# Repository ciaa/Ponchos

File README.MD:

#Poncho IOT (Internet Of Things) para EDU-CIAA-NXP 

##Características Poncho

  - Módulo Wifi RN1810. Se utiliza mediante comandos por el puerto serial.
  - Dos salidas a Rele 220V-10A
  - Dos entradas optoacopladas
  - Sensor de temperatura analógico LM35
  
##Características PCB

El PCB fue pensado para ser construido manualmente, por lo que solo posee una capa (BOTTOM). La capa TOP solo indica jumpers que deben soldarse. Tambien es posible fabricarla en dos capas.
  
##Modelo 3D

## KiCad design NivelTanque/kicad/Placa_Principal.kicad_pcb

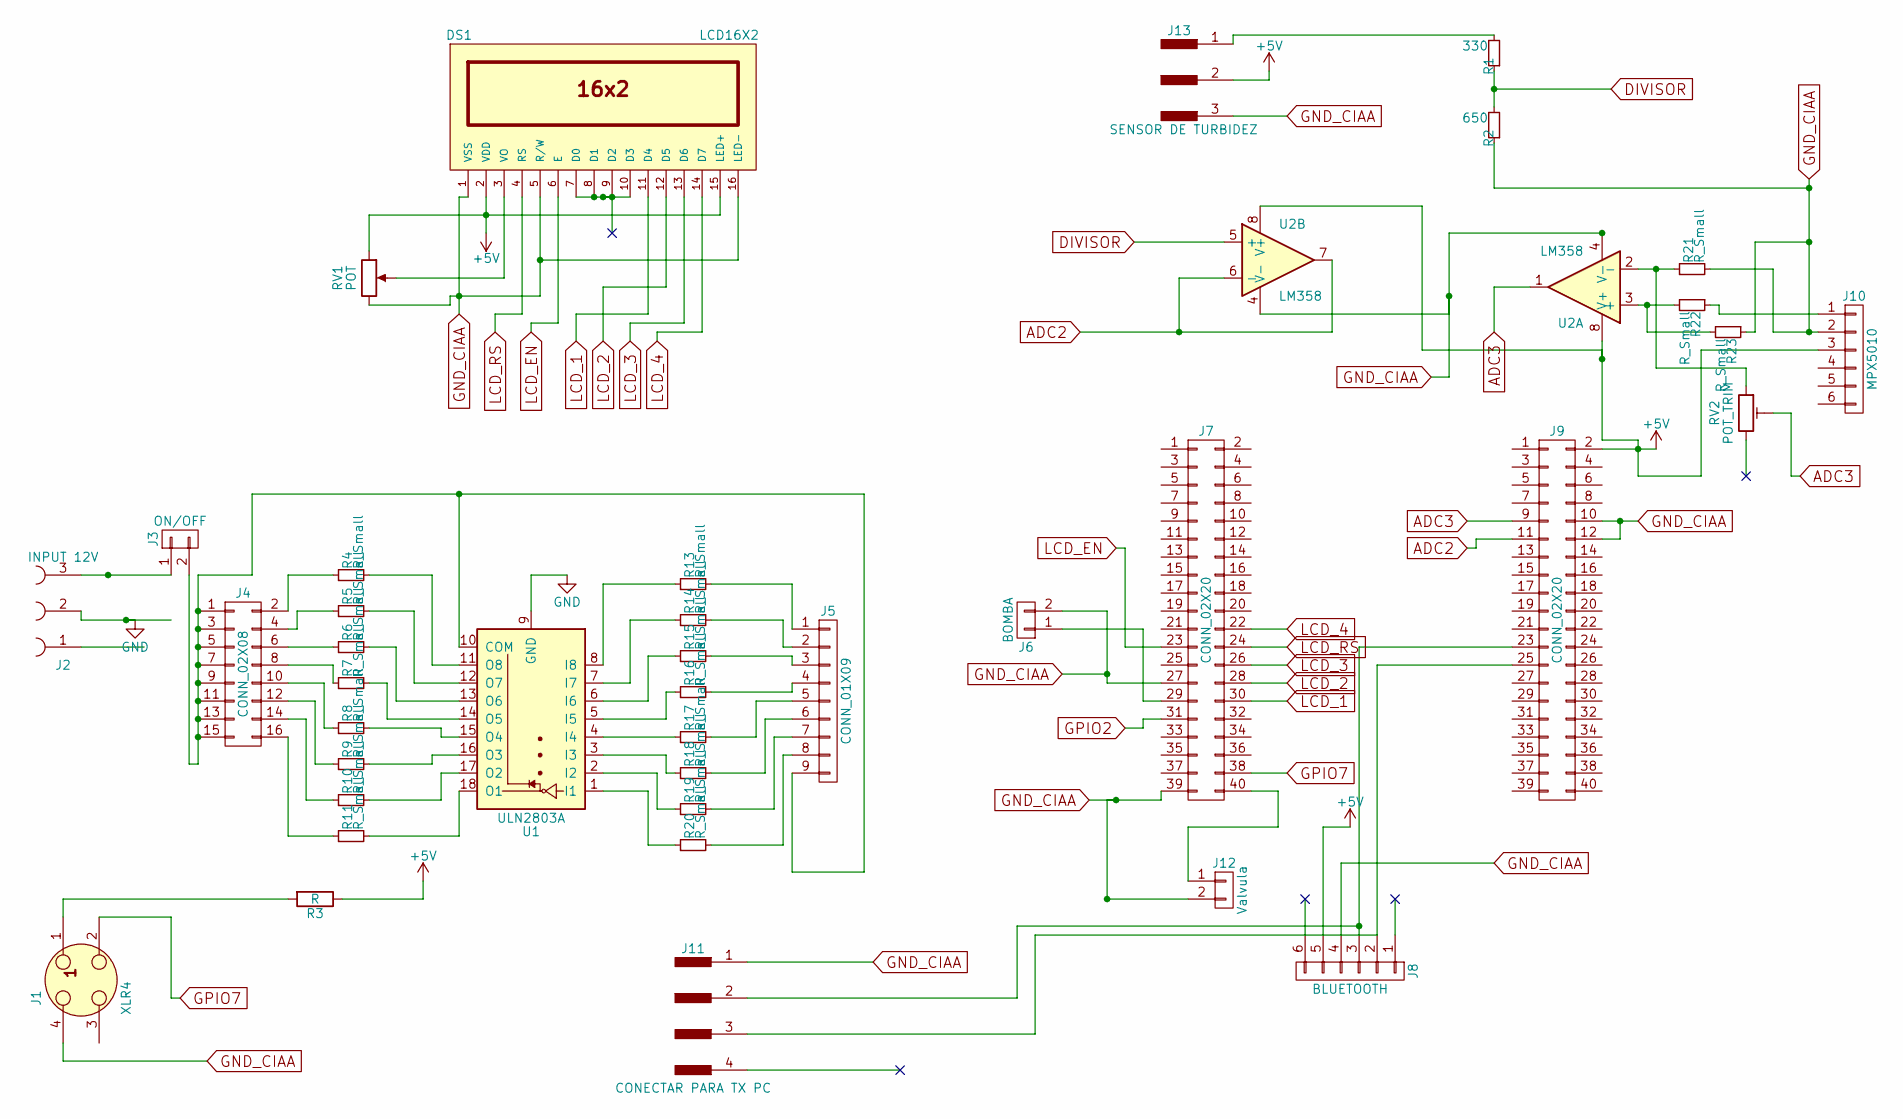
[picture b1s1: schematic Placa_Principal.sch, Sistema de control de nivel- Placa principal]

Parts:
DS1: LCD16X2; JST_XH_B16B-XH-A_16x2.50mm_Straight
J1: XLR4; Diode_Bridge_DIP-4_W7.62mm_P5.08mm
J2: INPUT 12V; TerminalBlock_bornier-3_P5.08mm
J3: ON/OFF; TerminalBlock_bornier-2_P5.08mm
J4: CONN_02X08; Pin_Header_Straight_2x08_Pitch2.54mm
J5: CONN_01X09; Pin_Header_Straight_1x09_Pitch2.54mm
J6: BOMBA; TerminalBlock_bornier-2_P5.08mm
J7, J9: CONN_02X20; Pin_Header_Straight_2x20_Pitch2.54mm
J8: BLUETOOTH; Pin_Header_Straight_1x06_Pitch2.54mm
J10: MPX5010; Pin_Header_Straight_1x06_Pitch2.54mm
J11: CONECTAR PARA TX PC; Pin_Header_Straight_1x04_Pitch2.54mm
J12: Valvula; TerminalBlock_bornier-2_P5.08mm
J13: SENSOR DE TURBIDEZ; Pin_Header_Straight_1x03_Pitch2.54mm
R1: 330; R_Axial_DIN0207_L6.3mm_D2.5mm_P15.24mm_Horizontal
R2: 650; R_Axial_DIN0207_L6.3mm_D2.5mm_P15.24mm_Horizontal
R3: R; R_Axial_DIN0207_L6.3mm_D2.5mm_P15.24mm_Horizontal
R4, R5, R6, R7, R8, R9, R10, R11, R13, R14, R15, R16, R17, R18, R19, R20, R21, R22, R23: R_Small; R_Axial_DIN0207_L6.3mm_D2.5mm_P15.24mm_Horizontal
RV1: POT; TerminalBlock_bornier-3_P5.08mm
RV2: POT_TRIM; Potentiometer_Trimmer_Bourns_3296W
U1: ULN2803A; DIP-18_W7.62mm_LongPads
U2: LM358; DIP-8_W7.62mm_LongPads

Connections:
+5V: DS1.2 (VDD), DS1.15 (LED+), J8.5, J9.2, J10.3, J13.2, R3.1, RV1.1, U2.8 (V+)
ADC2: J9.11, U2.6 (-), U2.7
ADC3: J9.9, RV2.2, U2.1
DIVISOR: R1.1, R2.2, U2.5 (+)
GND: J2.2, U1.9 (GND)
GND_CIAA: DS1.1 (VSS), DS1.5 (R/W), DS1.16 (LED-), J1.4, J6.2, J7.27, J7.39, J8.4, J9.10, J9.12, J10.2, J11.1, J12.2, J13.3, R2.1, R21.2, R23.1, RV1.3, U2.4 (V-)
GPIO2: J7.31
GPIO7: J1.2, J7.38
LCD_1: DS1.11 (D4), J7.30
LCD_2: DS1.12 (D5), J7.28
LCD_3: DS1.13 (D6), J7.26
LCD_4: DS1.14 (D7), J7.22
LCD_EN: DS1.6 (E), J7.23
LCD_RS: DS1.4 (RS), J7.24
unnamed: DS1.3 (VO), RV1.2
unnamed: DS1.7 (D0), DS1.8 (D1), DS1.9 (D2), DS1.10 (D3)
unnamed: J1.1, R3.2
unnamed: J2.3, J3.1
unnamed: J3.2, J4.1, J4.3, J4.5, J4.7, J4.9, J4.11, J4.13, J4.15, J5.9, U1.10 (COM)
unnamed: J4.2, R4.1
unnamed: J4.4, R5.1
unnamed: J4.6, R6.1
unnamed: J4.8, R7.1
unnamed: J4.10, R8.1
unnamed: J4.12, R9.1
unnamed: J4.14, R10.1
unnamed: J4.16, R11.1
unnamed: J5.1, R13.2
unnamed: J5.2, R14.2
unnamed: J5.3, R15.2
unnamed: J5.4, R16.2
unnamed: J5.5, R17.2
unnamed: J5.6, R18.2
unnamed: J5.7, R19.2
unnamed: J5.8, R20.2
unnamed: J6.1, J7.29
unnamed: J10.1, R22.1
unnamed: J8.3, J9.23, J11.2
unnamed: J8.2, J9.25, J11.3
unnamed: J7.40, J12.1
unnamed: J13.1, R1.2
unnamed: R4.2, U1.11 (O8)
unnamed: R5.2, U1.12 (O7)
unnamed: R6.2, U1.13 (O6)
unnamed: R7.2, U1.14 (O5)
unnamed: R8.2, U1.15 (O4)
unnamed: R9.2, U1.16 (O3)
unnamed: R10.2, U1.17 (O2)
unnamed: R11.2, U1.18 (O1)
unnamed: R13.1, U1.8 (I8)
unnamed: R14.1, U1.7 (I7)
unnamed: R15.1, U1.6 (I6)
unnamed: R16.1, U1.5 (I5)
unnamed: R17.1, U1.4 (I4)
unnamed: R18.1, U1.3 (I3)
unnamed: R19.1, U1.2 (I2)
unnamed: R20.1, U1.1 (I1)
unnamed: R21.1, RV2.1, U2.2 (-)
unnamed: R22.2, R23.2, U2.3 (+)

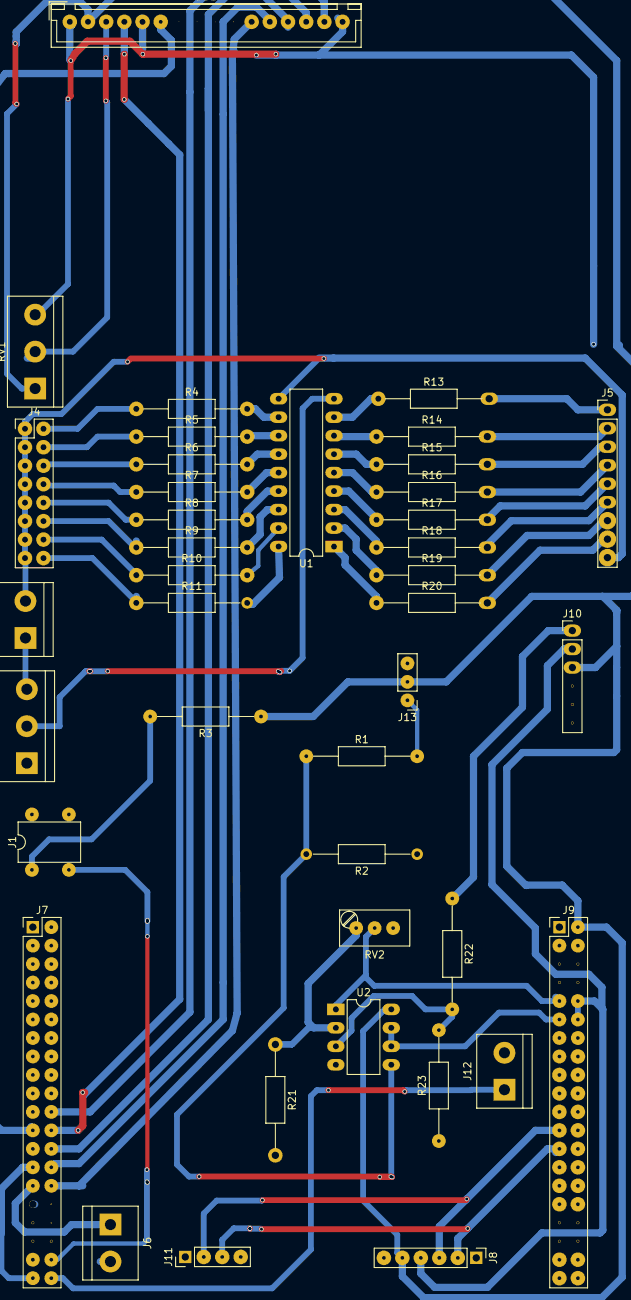
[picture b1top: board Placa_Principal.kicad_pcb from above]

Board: 2 copper layers, 40 parts (0 on the bottom side), 58 nets.

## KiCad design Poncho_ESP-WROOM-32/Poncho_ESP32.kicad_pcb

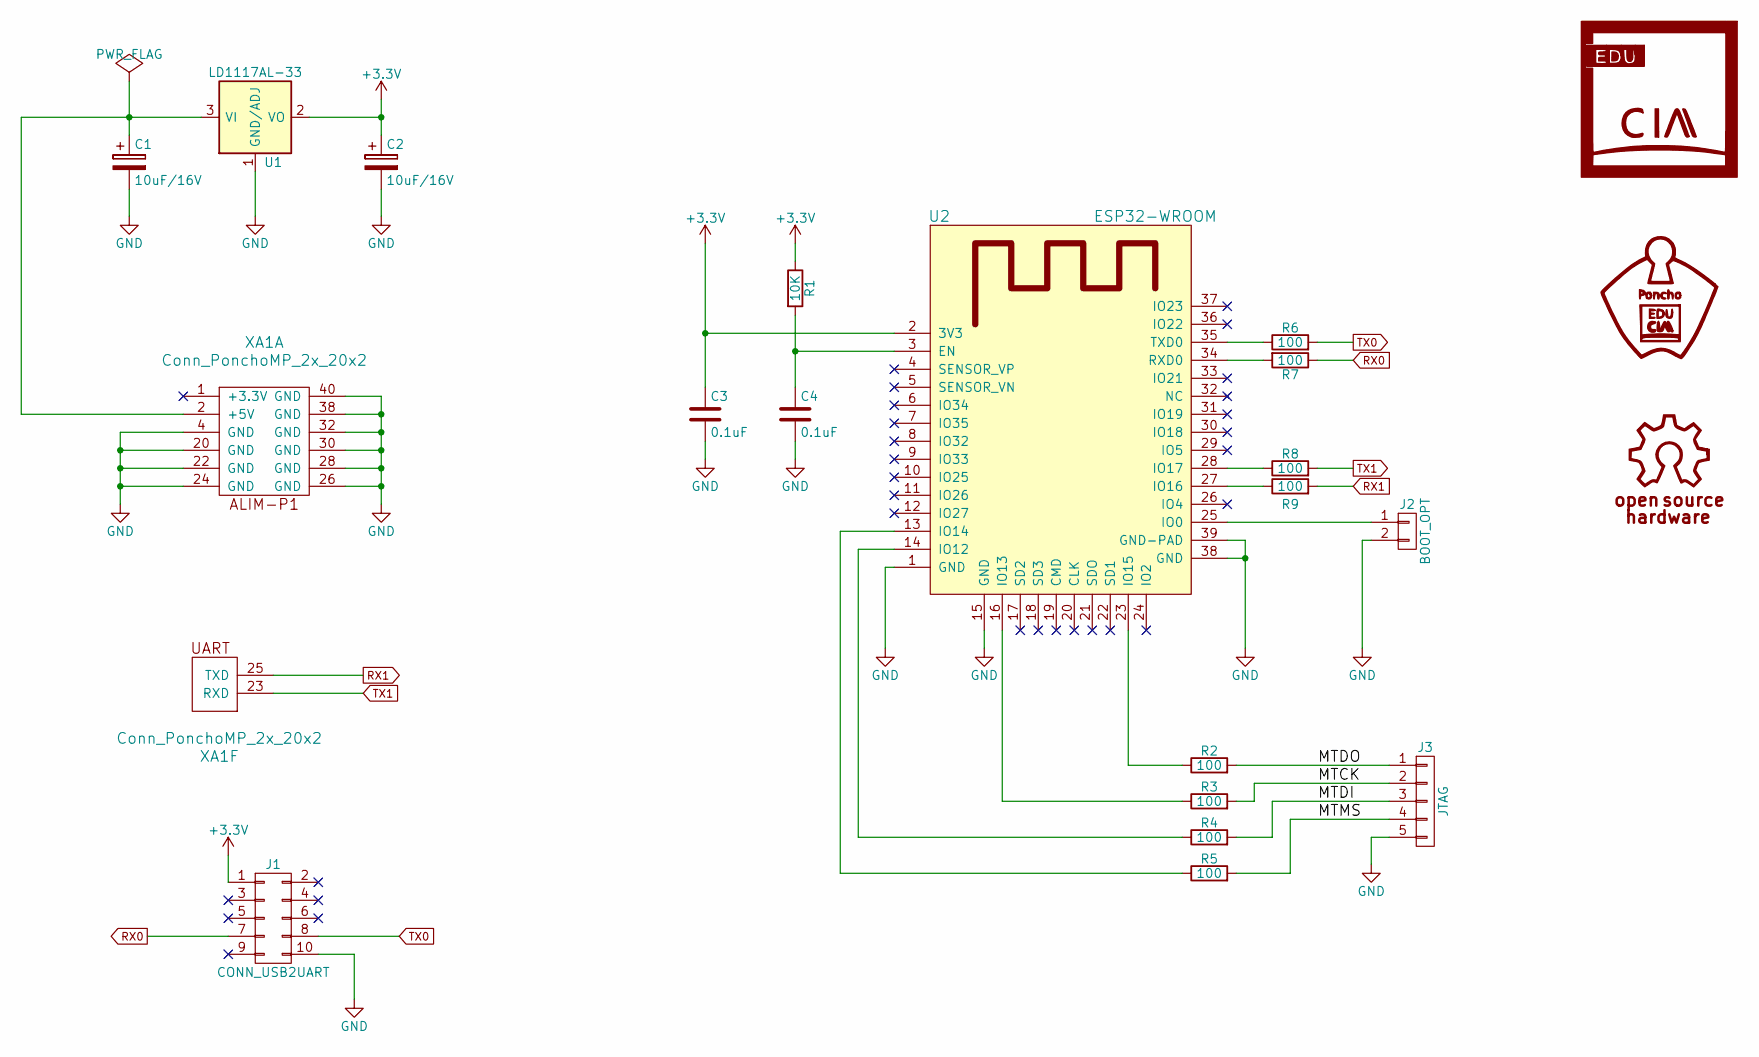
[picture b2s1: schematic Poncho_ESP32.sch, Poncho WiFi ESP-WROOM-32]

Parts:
C1, C2: 10uF/16V; CP_Elec_4x5.3
C3, C4: 0.1uF; C_0805_HandSoldering
J1: CONN_USB2UART; Socket_Strip_Angled_2x05_Pitch2.54mm
J2: BOOT_OPT; Pin_Header_Straight_1x02_Pitch2.54mm
J3: JTAG; Pin_Header_Straight_1x05_Pitch2.54mm
R1: 10K; R_0805_HandSoldering
R2, R3, R4, R5, R6, R7, R8, R9: 100; R_0805_HandSoldering
U1: LD1117AL-33; SOT-223
U2: ESP32-WROOM
XA1: Conn_PonchoMP_2x_20x2; Conn_Poncho_Derecha_Sin_Pin_Desc

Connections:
+3V3: C2.1, C3.1, J1.1, R1.1, U1.2 (VO), U1.4 (VO), U2.2 (3V3)
/MTCK: J3.2, R3.2
/MTDI: J3.3, R4.2
/MTDO: J3.1, R2.2
/MTMS: J3.4, R5.2
GND: C1.2, C2.2, C3.2, C4.2, J1.10, J2.2, J3.5, U1.1 (GND/ADJ), U2.1 (GND), U2.15 (GND), U2.38 (GND), U2.39 (GND-PAD), XA1.4 (GND), XA1.20 (GND), XA1.22 (GND), XA1.24 (GND), XA1.26 (GND), XA1.28 (GND), XA1.30 (GND), XA1.32 (GND), XA1.38 (GND), XA1.40 (GND)
unnamed: C1.1, U1.3 (VI), XA1.2 (+5V)
unnamed: C4.1, R1.2, U2.3 (EN)
unnamed: J2.1, U2.25 (IO0)
unnamed: R2.1, U2.23 (IO15)
unnamed: R3.1, U2.16 (IO13)
unnamed: R4.1, U2.14 (IO12)
unnamed: R5.1, U2.13 (IO14)
unnamed: R6.1, U2.35 (TXD0)
unnamed: R7.2, U2.34 (RXD0)
unnamed: R8.1, U2.28 (IO17)
unnamed: R9.1, U2.27 (IO16)
RX0: J1.7, R7.1
RX1: R9.2, XA1.25 (TXD)
TX0: J1.8, R6.2
TX1: R8.2, XA1.23 (RXD)

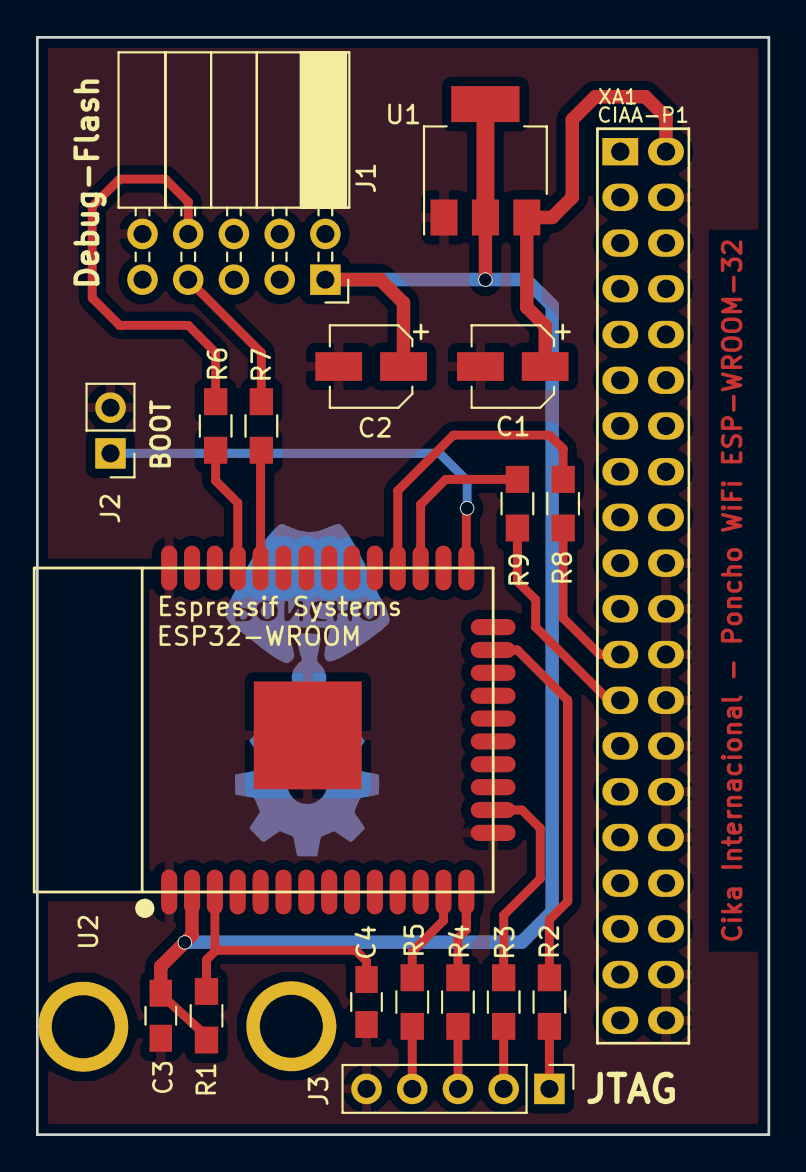
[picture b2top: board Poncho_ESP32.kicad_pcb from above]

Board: 2 copper layers, 40.6 x 61.0 mm, 21 parts (0 on the bottom side), 21 nets.

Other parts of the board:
H2, H2#2: PCB_HOLE; Led_Hole

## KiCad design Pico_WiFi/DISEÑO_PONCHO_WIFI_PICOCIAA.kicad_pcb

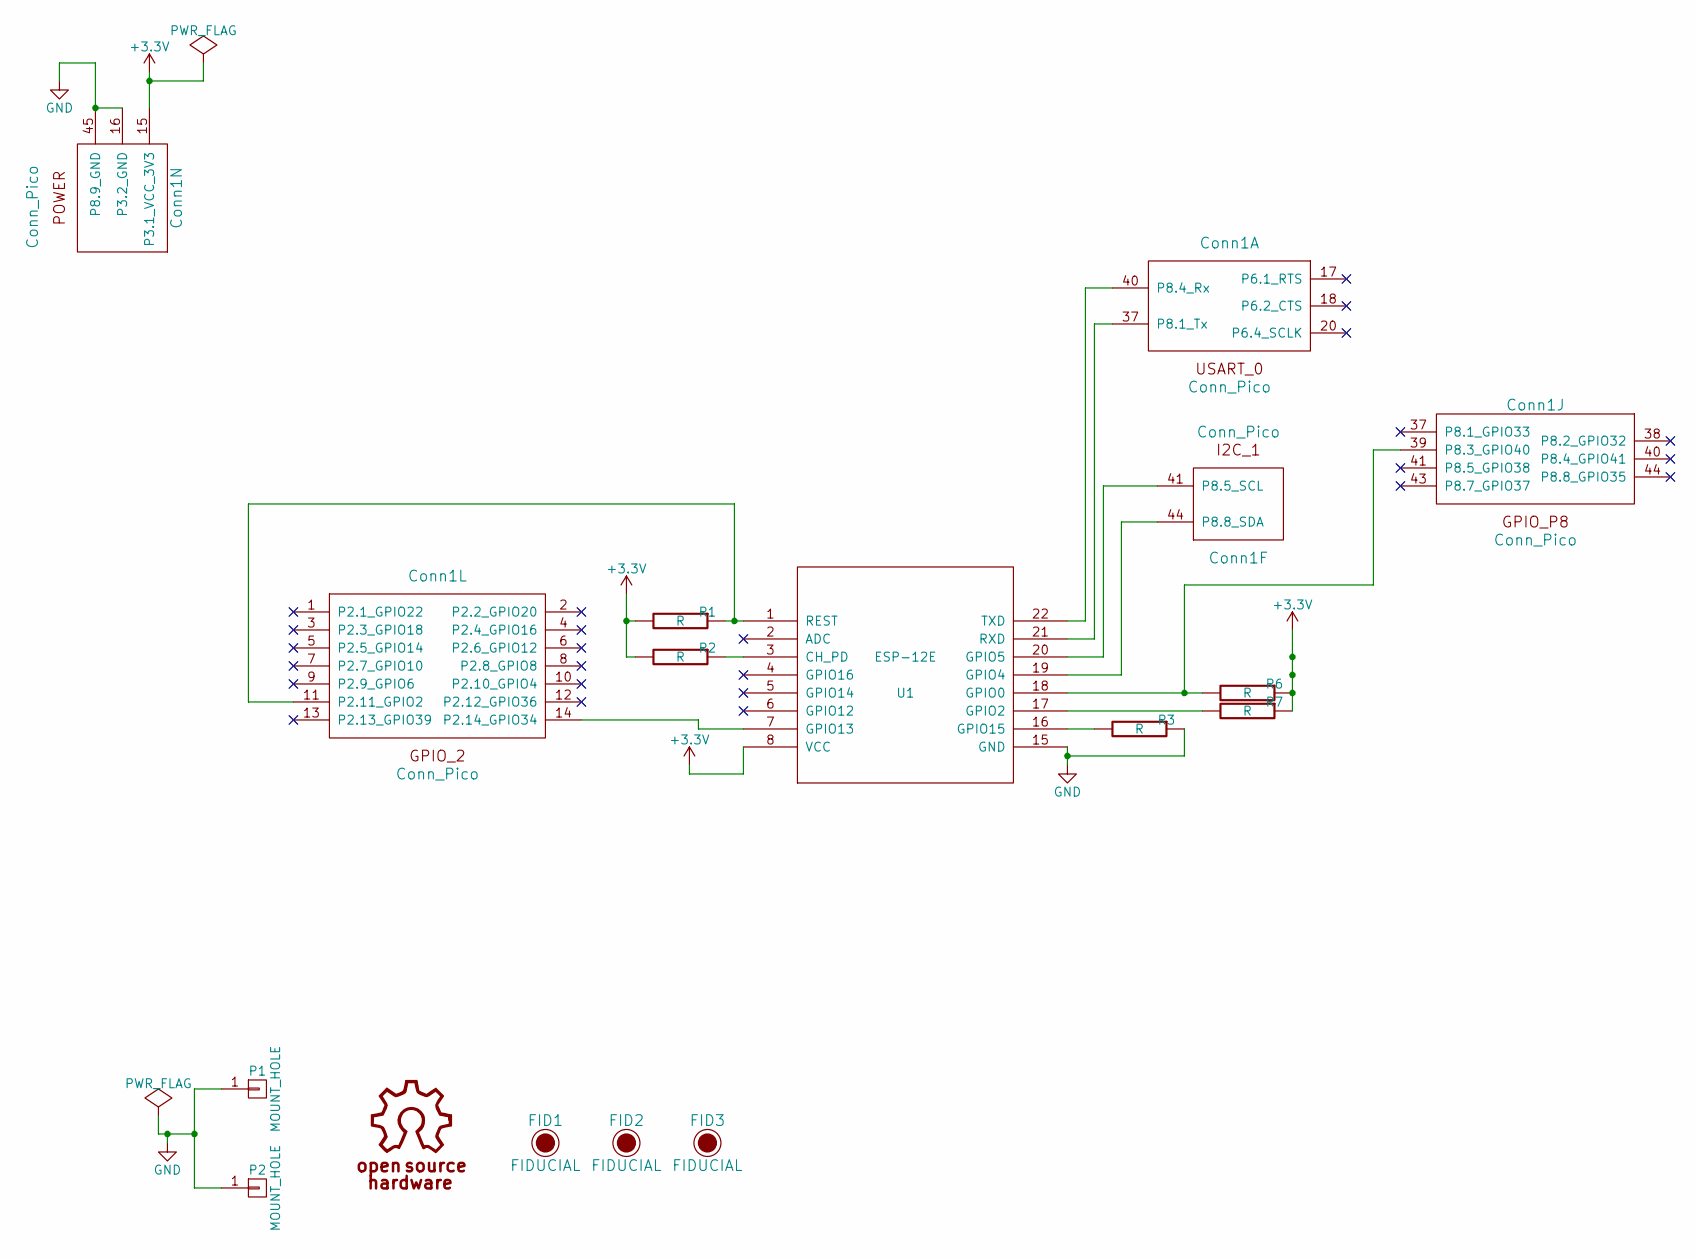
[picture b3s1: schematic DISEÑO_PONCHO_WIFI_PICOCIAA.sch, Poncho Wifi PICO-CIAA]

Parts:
Conn1: Conn_Pico; Conn_Pico_Ciaa; Digikey# Value
FID1, FID2, FID3: FIDUCIAL; Fiducial_1mm_Dia_2.54mm_Outer_CopperTop
P1, P2: MOUNT_HOLE; PIN_ARRAY_1
R1, R2, R3, R6, R7: R; R_0805_HandSoldering; Digikey# 1056-MCR10J103-CHP
U1: ESP-12E; Digikey# 1528-1438-ND

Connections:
+3V3: Conn1.15 (P3.1_VCC_3V3), R1.2, R2.2, R6.1, R7.1, U1.8 (VCC)
GND: Conn1.16 (P3.2_GND), Conn1.45 (P8.9_GND), P1.1, P2.1, R3.1, U1.15 (GND)
unnamed: Conn1.11 (P2.11_RTS), R1.1, U1.1 (REST)
unnamed: Conn1.14 (P2.14_GPIO34), U1.7 (GPIO13)
unnamed: Conn1.37 (P8.1_Tx), U1.21 (RXD)
unnamed: Conn1.39 (P8.3_SCL), R6.2, U1.18 (GPIO0)
unnamed: Conn1.40 (P8.4_Rx), U1.22 (TXD)
unnamed: Conn1.41 (P8.5_CTS), U1.20 (GPIO5)
unnamed: Conn1.44 (P8.8_SDA), U1.19 (GPIO4)
unnamed: R2.1, U1.3 (CH_PD)
unnamed: R3.2, U1.16 (GPIO15)
unnamed: R7.2, U1.17 (GPIO2)

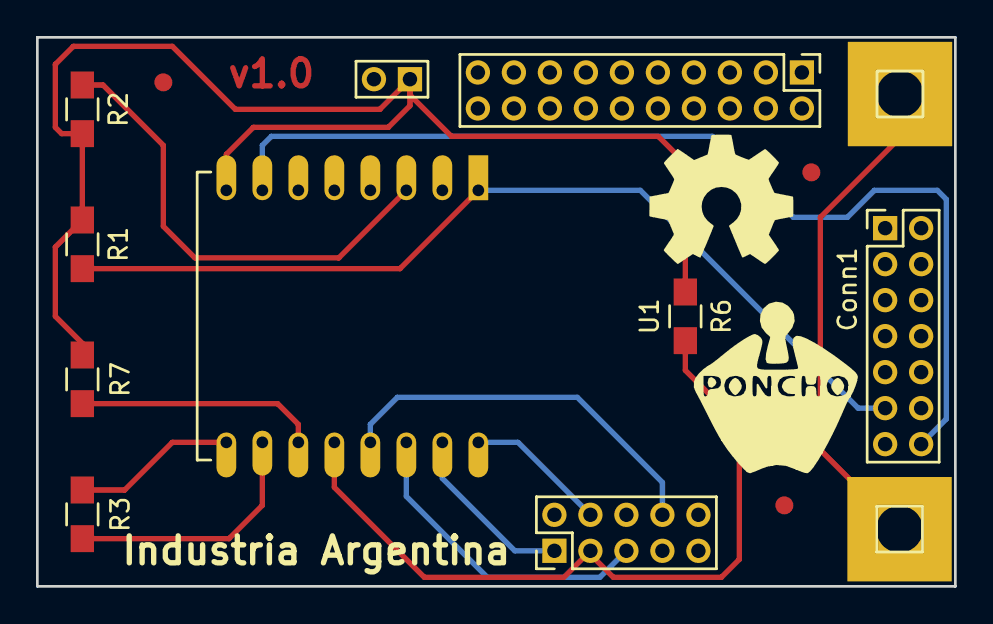
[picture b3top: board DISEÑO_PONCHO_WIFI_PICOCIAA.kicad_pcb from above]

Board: 2 copper layers, 51.0 x 30.5 mm, 13 parts (0 on the bottom side), 12 nets.

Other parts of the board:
G101: Logo_OSHWA

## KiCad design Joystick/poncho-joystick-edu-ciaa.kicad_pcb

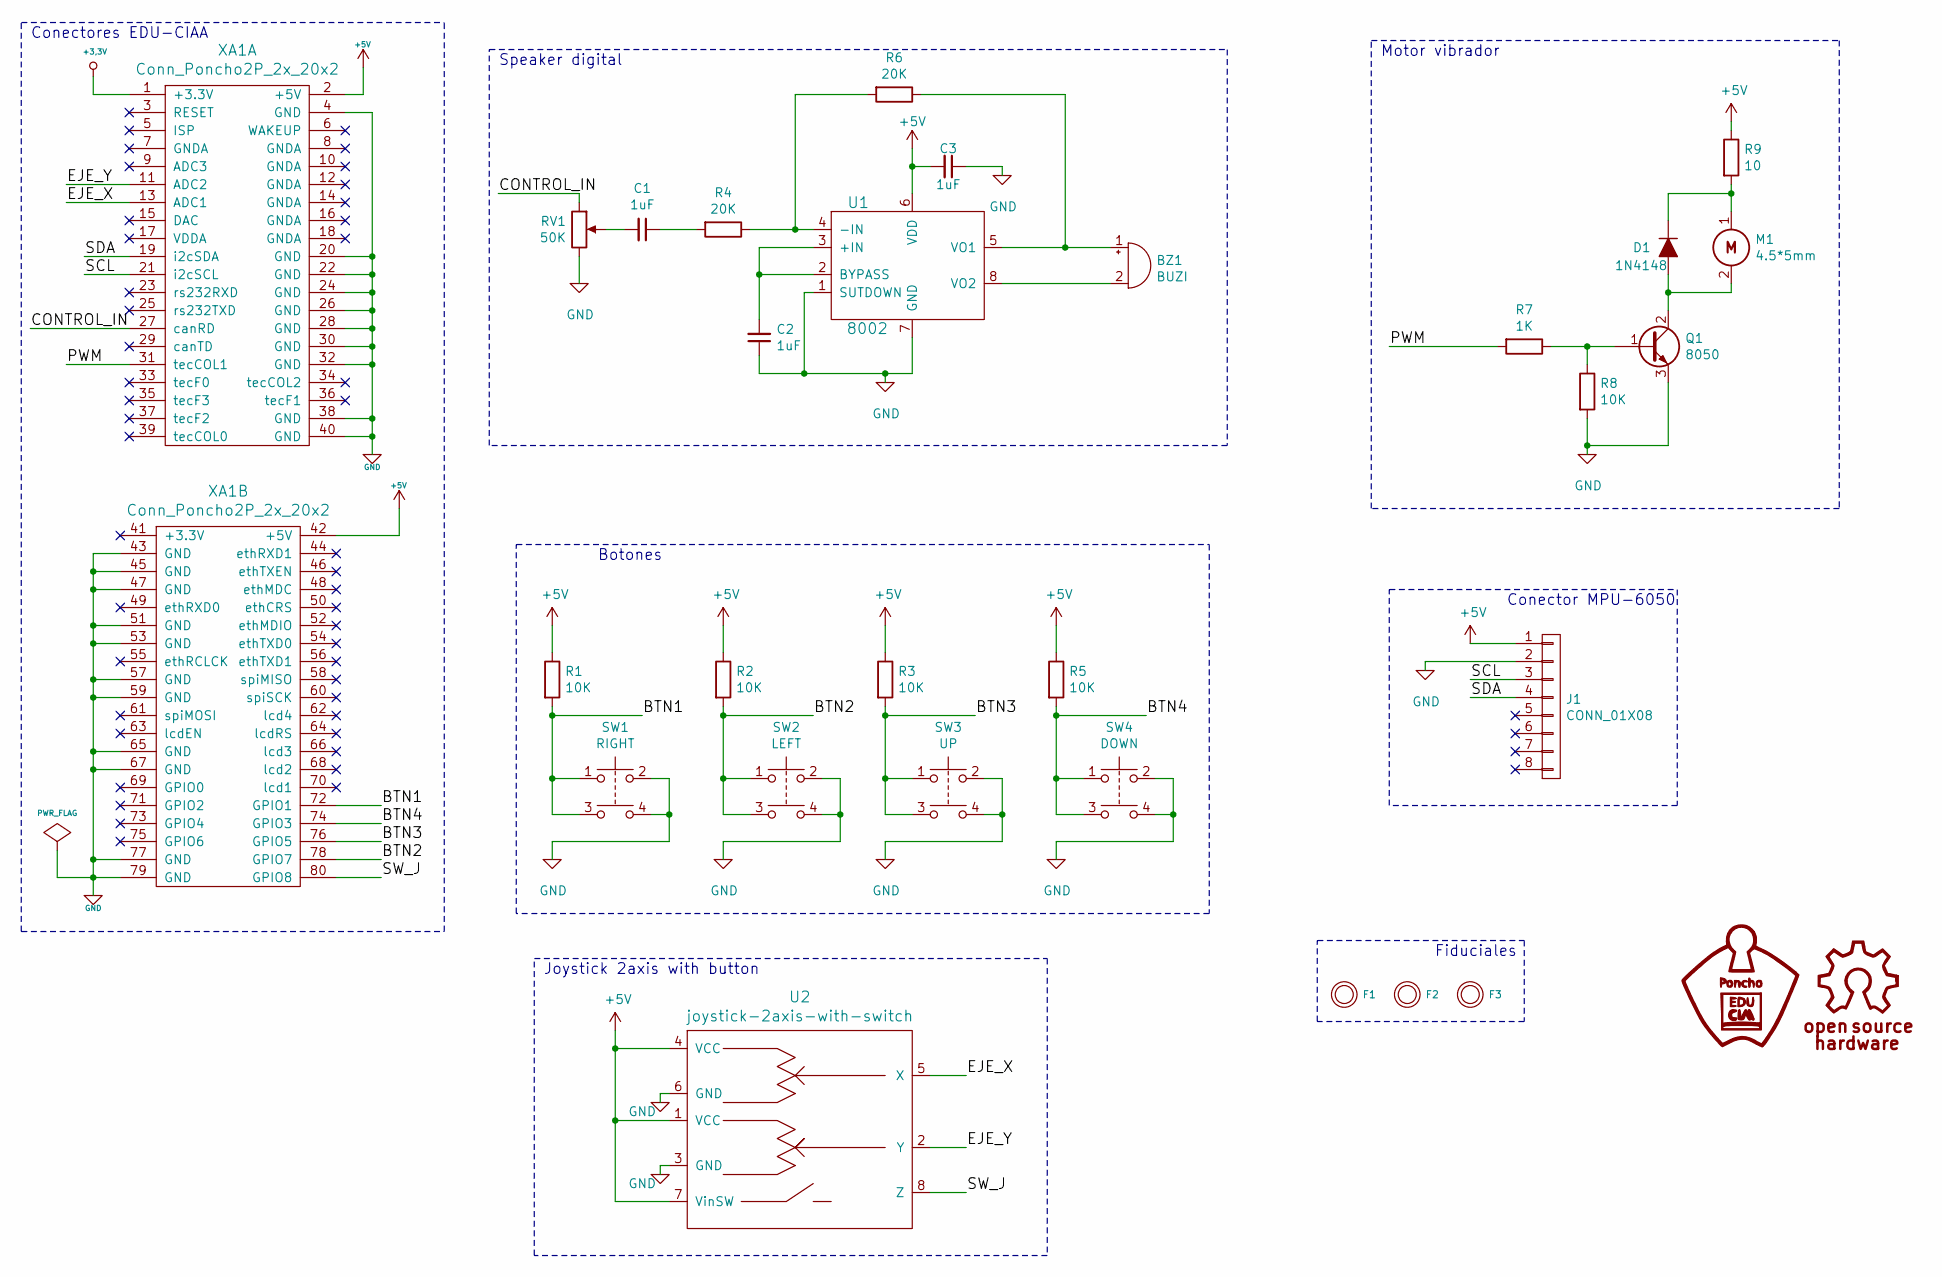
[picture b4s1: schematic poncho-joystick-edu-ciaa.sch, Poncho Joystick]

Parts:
BZ1: BUZI; Buzzer_12x9.5RM7.6; DigiKey# 102-2502-ND
C1, C2, C3: 1uF; C_0805_HandSoldering; DigiKey# 490-1536-2-ND
D1: 1N4148; D_0805; DigiKey# CD0603-S01575TR-ND
F1, F2, F3: FIDUCIAL; Fiducial_1mm
J1: CONN_01X08; adxl345
M1: 4.5*5mm; Vibration_motor; DigiKey# P122157-ND
Q1: 8050; SOT-23_Handsoldering; DigiKey# MMSS8050-L-TPMSTR-ND
R1, R2, R3, R5, R8: 10K; R_0805_HandSoldering; DigiKey# 311-10KERTR-ND
R4, R6: 20K; R_0805_HandSoldering; DigiKey# 311-20KERTR-ND
R7: 1K; R_0805_HandSoldering; DigiKey# 311-1.00KFRTR-ND
R9: 10; R_0805_HandSoldering; DigiKey# 311-10.0FRTR-ND
RV1: 50K; Potentiometer_Trimmer-EVM3E; DigiKey# ST32ETB503TR-ND
SW1: RIGHT; SW_SPST_KMR2; DigiKey# CKN10246TR-ND
SW2: LEFT; SW_SPST_KMR2; DigiKey# CKN10246TR-ND
SW3: UP; SW_SPST_KMR2; DigiKey# CKN10246TR-ND
SW4: DOWN; SW_SPST_KMR2; DigiKey# CKN10246TR-ND
U1: 8002; AD8002; DigiKey# AD8002ARMZ-ND
U2: joystick-2axis-with-switch; joystick-2axis-withswitch; DigiKey# 254SA103B50B-ND
XA1: Conn_Poncho2P_2x_20x2; Conn_Poncho_Completo_Modificado

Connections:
+3.3V: XA1.1 (+3.3V)
+5V: C3.2, J1.1, R1.1, R2.1, R3.1, R5.1, R9.1, U1.6 (VDD), U2.1 (VCC), U2.4 (VCC), U2.7 (VinSW), XA1.2 (+5V), XA1.42 (+5V)
/BTN1: R1.2, SW1.1, SW1.3, XA1.72 (GPIO1)
/BTN2: R2.2, SW2.1, SW2.3, XA1.78 (GPIO7)
/BTN3: R3.2, SW3.1, SW3.3, XA1.76 (GPIO5)
/BTN4: R5.2, SW4.1, SW4.3, XA1.74 (GPIO3)
/CONTROL_IN: RV1.1, XA1.27 (canRD)
/EJE_X: U2.5 (X), XA1.13 (ADC1)
/EJE_Y: U2.2 (Y), XA1.11 (ADC2)
/PWM: R7.2, XA1.31 (tecCOL1)
/SCL: J1.3, XA1.21 (i2cSCL)
/SDA: J1.4, XA1.19 (i2cSDA)
/SW_J: U2.8 (Z), XA1.80 (GPIO8)
GND: C2.1, C3.1, J1.2, Q1.3 (E), R8.2, RV1.3, SW1.2, SW1.4, SW2.2, SW2.4, SW3.2, SW3.4, SW4.2, SW4.4, U1.1 (SUTDOWN), U1.7 (GND), U2.3 (GND), U2.6 (GND), XA1.4 (GND), XA1.20 (GND), XA1.22 (GND), XA1.24 (GND), XA1.26 (GND), XA1.28 (GND), XA1.30 (GND), XA1.32 (GND), XA1.38 (GND), XA1.40 (GND), XA1.43 (GND), XA1.45 (GND), XA1.47 (GND), XA1.51 (GND), XA1.53 (GND), XA1.57 (GND), XA1.59 (GND), XA1.65 (GND), XA1.67 (GND), XA1.77 (GND), XA1.79 (GND)
unnamed 14: BZ1.1 (-), R6.1, U1.5 (VO1); also elsewhere on the board
unnamed 15: BZ1.2 (+), U1.8 (VO2); also elsewhere on the board
unnamed: C1.1, R4.2
unnamed: C1.2, RV1.2
unnamed: C2.2, U1.2 (BYPASS), U1.3 (+IN)
unnamed: D1.1 (K), M1.1 (+), R9.2
unnamed: D1.2 (A), M1.2 (-), Q1.2 (C)
unnamed: Q1.1 (B), R7.1, R8.1
unnamed: R4.1, R6.2, U1.4 (-IN)

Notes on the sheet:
Speaker digital
Motor vibrador
Botones
Conector MPU-6050
Conectores EDU-CIAA
Joystick 2axis with button
Fiduciales

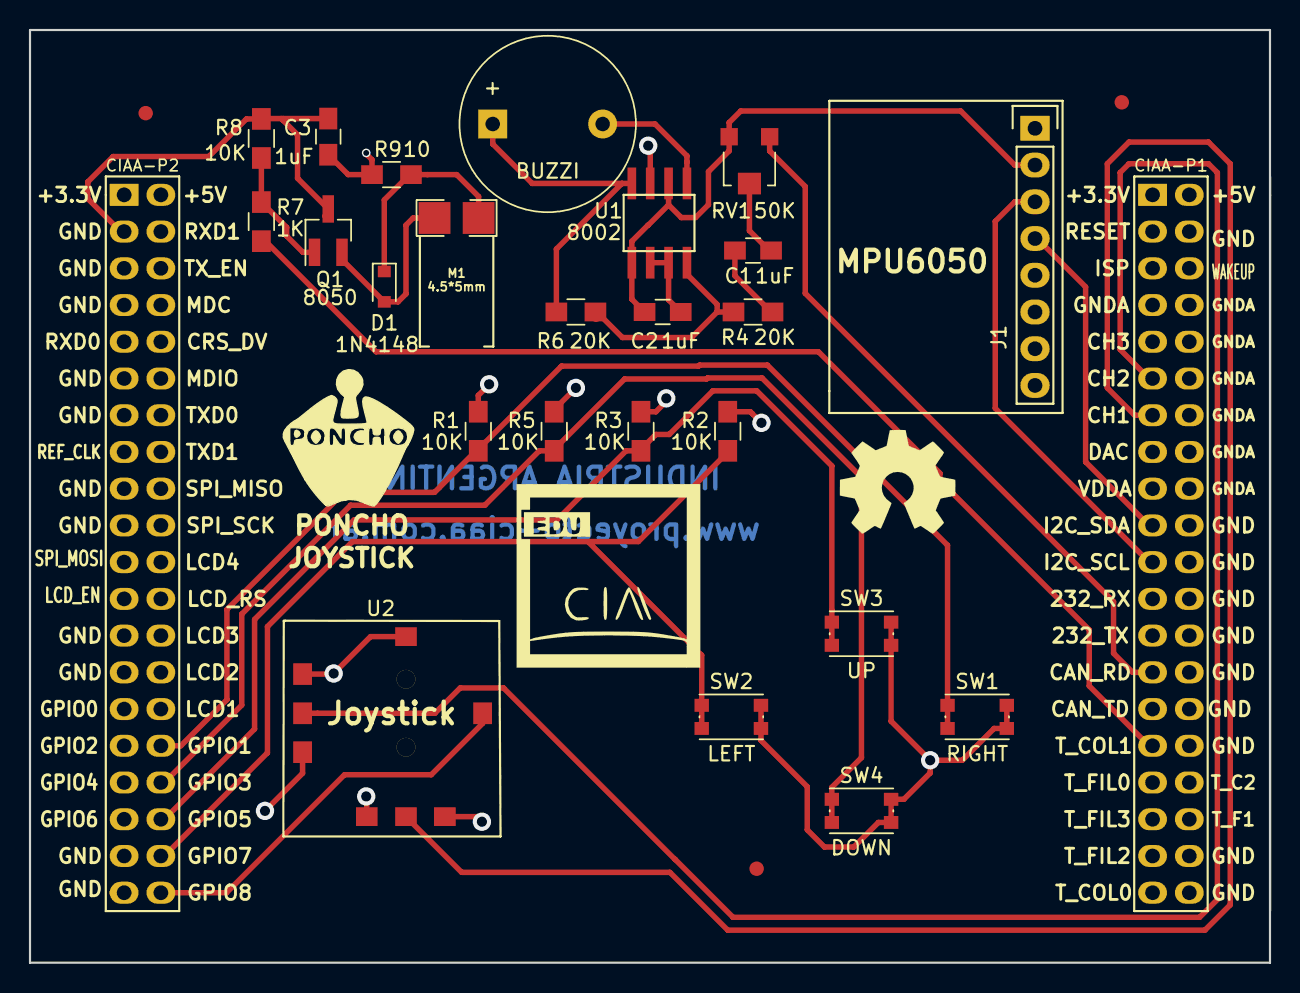
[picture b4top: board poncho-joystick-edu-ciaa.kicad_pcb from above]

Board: 2 copper layers, 85.8 x 64.5 mm, 29 parts (0 on the bottom side), 22 nets.

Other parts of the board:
BUZZI: BUZI; Buzzer_12x9.5RM7.6
PONCHO: JOYSTICK; Logo_Poncho

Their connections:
unnamed 14: BUZZI.1; also elsewhere on the board
unnamed 15: BUZZI.2; also elsewhere on the board

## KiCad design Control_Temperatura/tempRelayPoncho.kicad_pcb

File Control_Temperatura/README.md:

# TPdesign_poncho
Nombre corto del proyecto: 
Interfaz de termocupla K mas salidas a Relay

Autor:
Francisco Suárez

Fecha de este documento::

28 Mayo de 2017

Licencia:
BSD
GPL V3, Open Hardware

Descripción:
Es una poncho destinado a intermediar con termocuplas mas el control de dos interruptores a traves de relays, pensado para hacer control de temperatura en un tanque de agua a travez de resistencias.

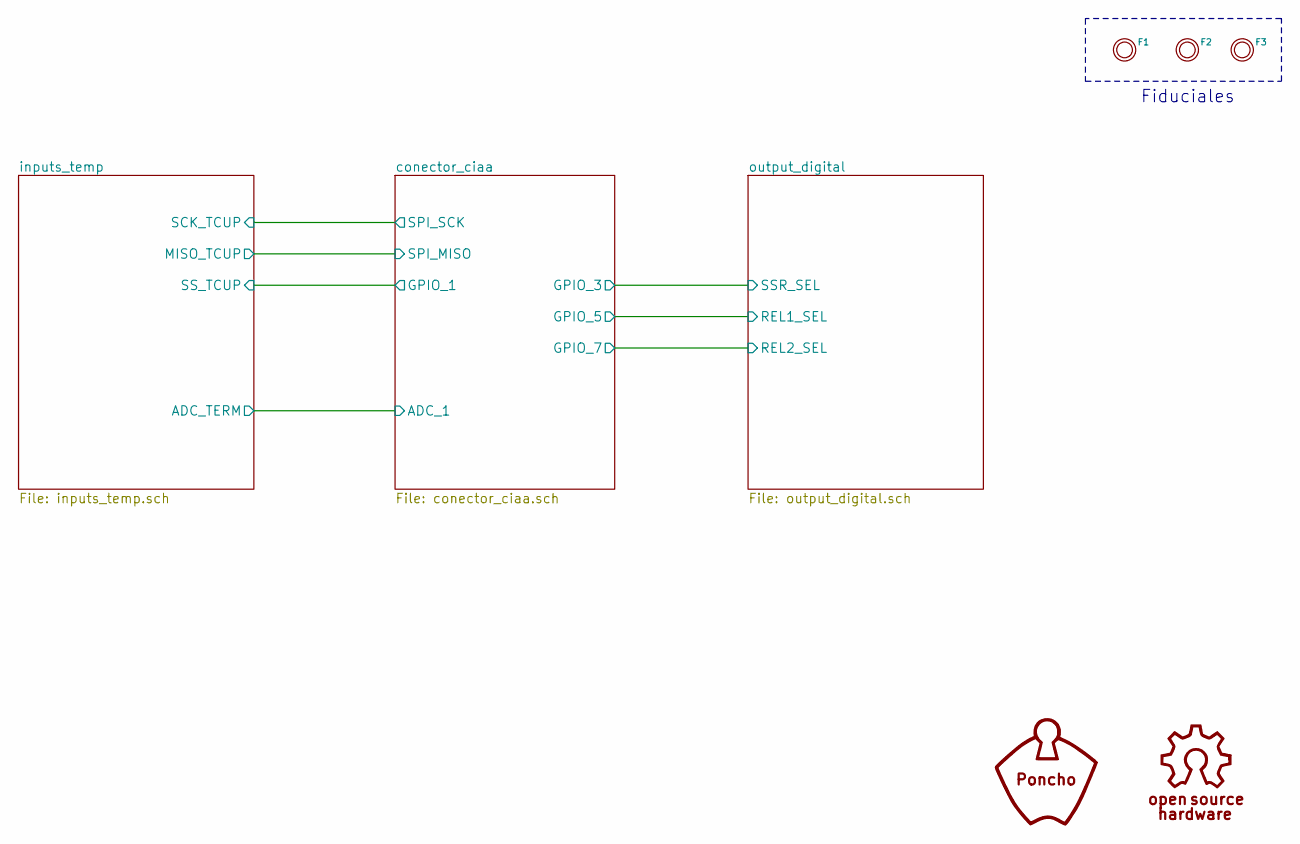
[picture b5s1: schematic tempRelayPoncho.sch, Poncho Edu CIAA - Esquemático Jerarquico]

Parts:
F1, F2, F3: FIDUCIAL; Fiducial_1mm

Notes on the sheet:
Fiduciales

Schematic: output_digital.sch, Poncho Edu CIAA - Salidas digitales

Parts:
D1: RELAY_1; LED-0805; Mouser# Value; Digikey# 1080-1412-2-ND
D2: RELAY_2; LED-0805; Mouser# Value; Digikey# 1080-1412-2-ND
D3, D4: MRA4003T3G; DO-214AA(SMB); Mouser# Value; Digikey# MRA4003T3GOSTR-ND
D5: SSR_OUT; LED-0805; Mouser# Value; Digikey# 1080-1412-2-ND
J4, J5, J6: Screw_Terminal_1x02; TerminalBlock_Pheonix_MKDS1.5-2pol; Mouser# Value; Digikey# 277-5719-ND
Q1, Q2: MMBT3904; SOT23_NPN; Mouser# Value; Digikey# MMBT3904FSCT-ND
R2, R3, R4, R5, R8: 1k; R_0805_HandSoldering; Mouser# 603-RC0805FR-071KL; Digikey# 311-1.00KCRCT-ND
R6, R7: 10k; R_0805_HandSoldering; Mouser# 603-RC0805FR-0710KL; Digikey# 311-10.0KCRCT-ND
R9: 100; R_0805_HandSoldering; Mouser# 603-RC0805FR-07100RL; Digikey# 311-100CRCT-ND
U4, U6: G5LE-1A-5DC; Relay_G5LE-1A-5DC-5mm; Mouser# 653-G5LE-1ADC5; Digikey# Z3115-ND

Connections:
+5VD: D3.2, D4.2, R2.2, R3.2, U4.5, U6.5; also elsewhere on the board
/conector_ciaa/GPIO_3: R8.2, R9.2; also elsewhere on the board
/conector_ciaa/GPIO_5: R4.2; also elsewhere on the board
/conector_ciaa/GPIO_7: R5.2; also elsewhere on the board
GND: D5.1, J4.1, Q1.2, Q2.2, R6.1, R7.1; also elsewhere on the board
unnamed: D1.1, D3.1, Q1.3, U4.1
unnamed: D1.2, R2.1
unnamed: D2.1, D4.1, Q2.3, U6.1
unnamed: D2.2, R3.1
unnamed: D5.2, R8.1
unnamed: J4.2, R9.1
unnamed: J5.1, U4.3
unnamed: J5.2, U4.4
unnamed: J6.1, U6.3
unnamed: J6.2, U6.4
unnamed: Q1.1, R4.1, R7.2
unnamed: Q2.1, R5.1, R6.2

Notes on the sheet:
Salida SSR (Solid State Realy)
Salidas a Relay - 16A - 440VAC, 300VDC

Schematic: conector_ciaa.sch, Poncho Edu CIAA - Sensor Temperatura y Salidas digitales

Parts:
XA1: Conn_Poncho2P_2x_20x2; Conn_Poncho_Completo

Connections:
+3V3: XA1.41 (+3.3V); also elsewhere on the board
+5V: XA1.2 (+5V); also elsewhere on the board
+5VD: XA1.42 (+5V); also elsewhere on the board
/conector_ciaa/ADC_1: XA1.13 (ADC1); also elsewhere on the board
/conector_ciaa/GPIO_1: XA1.72 (GPIO1); also elsewhere on the board
/conector_ciaa/GPIO_3: XA1.74 (GPIO3); also elsewhere on the board
/conector_ciaa/GPIO_5: XA1.76 (GPIO5); also elsewhere on the board
/conector_ciaa/GPIO_7: XA1.78 (GPIO7); also elsewhere on the board
/inputs_temp/MISO_TCUP: XA1.58 (spiMISO); also elsewhere on the board
/inputs_temp/SCK_TCUP: XA1.60 (spiSCK); also elsewhere on the board
GND: XA1.4 (GND), XA1.20 (GND), XA1.22 (GND), XA1.24 (GND), XA1.26 (GND), XA1.28 (GND), XA1.30 (GND), XA1.32 (GND), XA1.38 (GND), XA1.40 (GND), XA1.43 (GND), XA1.45 (GND), XA1.47 (GND), XA1.51 (GND), XA1.53 (GND), XA1.57 (GND), XA1.59 (GND), XA1.65 (GND), XA1.67 (GND), XA1.77 (GND), XA1.79 (GND); also elsewhere on the board
GNDA: XA1.8 (GNDA), XA1.10 (GNDA), XA1.12 (GNDA), XA1.14 (GNDA), XA1.16 (GNDA), XA1.18 (GNDA); also elsewhere on the board

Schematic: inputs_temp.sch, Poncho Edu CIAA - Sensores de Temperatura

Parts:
C1, C3, C4: 10u; C_0805_HandSoldering; Mouser# 81-GRM21BR60J106ME19; Digikey# 490-1718-1-ND
C2, C5, C6: 100n; C_0805_HandSoldering; Mouser# 81-GRM21B7U1A104JA1L; Digikey# 490-11592-1-ND
J1, J2, J3: Screw_Terminal_1x02; TerminalBlock_Pheonix_MKDS1.5-2pol; Mouser# Value; Digikey# 277-5719-ND
R1: 10k; R_0805_HandSoldering; Mouser# 603-RC0805FR-0710KL; Digikey# 311-10.0KCRCT-ND
U1: NUP2105LT1G; SOT23_NPN; Mouser# Value; Digikey# NUP2105LT1GOSCT-ND
U2: MAX31855KASA+; SOIC-8; Mouser# Value; Digikey# MAX31855KASA+-ND
U3: MCP601R; SOT-23-5_HandSoldering; Mouser# 579-MCP601T-I/OT; Digikey# Value

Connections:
+3V3: C3.2, C5.2, U2.4; also elsewhere on the board
+5V: C4.2, C6.2, J2.1, U3.2; also elsewhere on the board
/conector_ciaa/ADC_1: U3.1, U3.4; also elsewhere on the board
/conector_ciaa/GPIO_1: U2.6; also elsewhere on the board
/inputs_temp/MISO_TCUP: U2.7; also elsewhere on the board
/inputs_temp/SCK_TCUP: U2.5; also elsewhere on the board
GND: C1.1, C3.1, C4.1, C5.1, C6.1, U1.3, U2.1, U3.5; also elsewhere on the board
GNDA: J3.2; also elsewhere on the board
unnamed: C1.2, R1.1, U3.3
unnamed: C2.1, J1.2, U1.2, U2.3
unnamed: C2.2, J1.1, U1.1, U2.2
unnamed: J2.2, J3.1, R1.2

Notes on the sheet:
Entrada Termoresistor
Entrada Termocupla
Resistor de Referencia

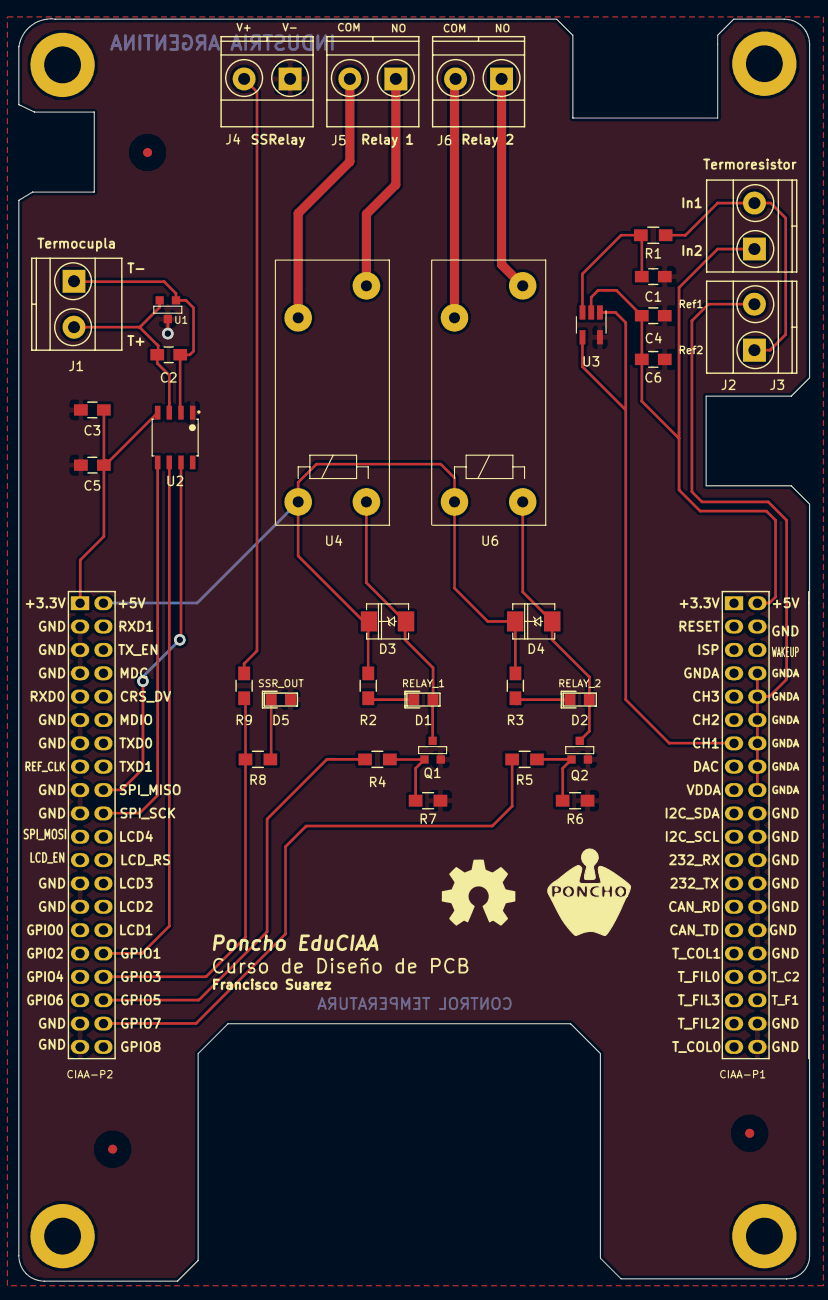
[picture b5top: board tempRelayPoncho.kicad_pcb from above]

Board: 2 copper layers, 86.0 x 137.3 mm, 38 parts (0 on the bottom side), 28 nets.

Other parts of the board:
G101: Logo_OSHWA
